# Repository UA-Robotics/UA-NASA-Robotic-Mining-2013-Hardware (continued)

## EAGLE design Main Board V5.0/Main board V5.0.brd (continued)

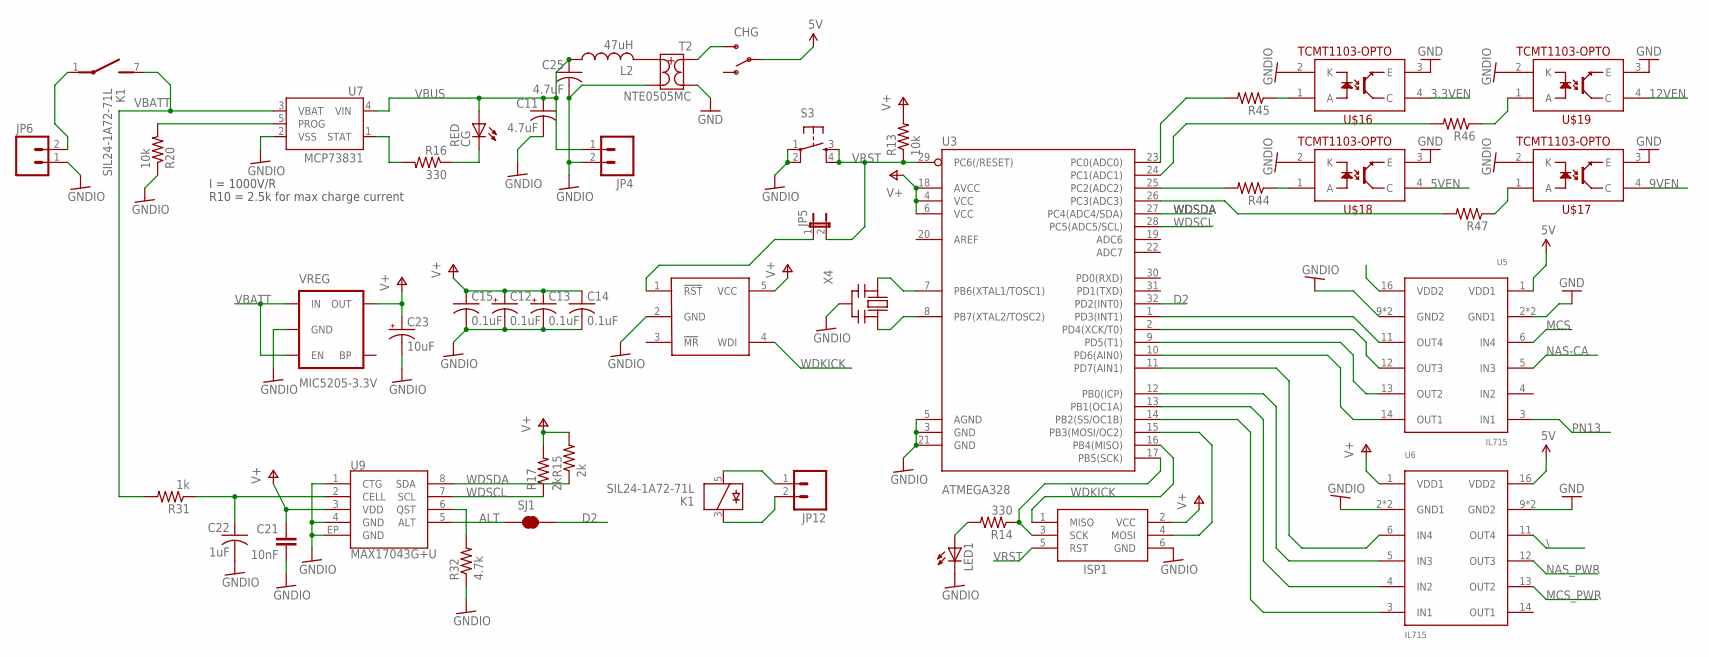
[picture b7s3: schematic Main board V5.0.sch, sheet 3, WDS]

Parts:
C11, C25: 4.7uF; C0603
C12, C13: 0.1uF; CT3528
C14, C15: 0.1uF; C0805
C21: 10nF; 0603-CAP
C22: 1uF; C0603
C23: 10uF; CT3528
CG: RED; SML0805
CHG: SWITCH-SPSTPTH; SWITCH-SPDT
ISP1: AVRISP-6; AVRISP
JP4: M021X02_NO_SILK; 1X02_NO_SILK
JP5: JUMPER-2PTH_LOCK; 1X02_LOCK
JP6: M02-JST-2MM-SMT; JST-2-SMD
JP12: M02POLAR_LOCK; MOLEX-1X2_LOCK
K1: SIL24-1A72-71L; REED
L2: 47uH; L2012C
LED1: LEDCHIPLED_0805; CHIPLED_0805
R13, R20: 10k; R0805
R14, R16: 330; R0805
R15, R17: 2k; R0805
R31: 1k; R0805
R32: 4.7k; R0805
R44, R45, R46, R47: R-US_R0805; R0805
S3: TAC_SWITCHPTH; TACTILE-PTH
SJ1: SOLDERJUMPERTRACE; SJ_2S-TRACE
T2: NTE0505MC; SO-8FT
U3: ATMEGA328; TQFP32-08
U5, U6: IL715; S016
U7: MCP73831; SOT23-5
U9: MAX17043G+U; TDFN-8
U20: MAX823; SOT23-5L
U$16, U$17, U$18, U$19: TCMT1103-OPTO; SSOP-4
VREG: MIC5205-3.3V; SOT23-5
X4: CERMOSCILL-AWCSR; AWCSR

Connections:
3.3VEN: U$16.4 (C); also elsewhere on the board
5V: CHG.2, U5.1 (VDD1), U6.16 (VDD2); also elsewhere on the board
5VEN: U$18.4 (C); also elsewhere on the board
9VEN: U$17.4 (C); also elsewhere on the board
12VEN: U$19.4 (C); also elsewhere on the board
ALT: SJ1.1, U9.5 (ALT)
CELL: C22.1, R31.1, U9.2 (CELL)
D2: SJ1.2, U3.32 (PD2(INT0))
GND: T2.1 (2), U5.2 (GND1), U5.8 (GND1), U6.9 (GND2), U6.15 (GND2), U$16.3 (E), U$17.3 (E), U$18.3 (E), U$19.3 (E); also elsewhere on the board
GNDIO: C11.2, C12.-, C13.-, C14.2, C15.2, C21.2, C22.2, C23.-, C25.2, ISP1.6 (GND), JP4.2, JP6.1, LED1.C, R20.1, R32.1, S3.1, S3.2, T2.7 (3), U3.3 (GND), U3.5 (AGND), U3.21 (GND), U5.9 (GND2), U5.15 (GND2), U6.2 (GND1), U6.8 (GND1), U7.2 (VSS), U9.1 (CTG), U9.4 (GND), U9.EP (GND), U20.2 (GND), U$16.2 (K), U$17.2 (K), U$18.2 (K), U$19.2 (K), VREG.2 (GND), X4.2 (GND)
MCS: U5.6 (IN4); also elsewhere on the board
MCS_PWR: U6.13 (OUT2); also elsewhere on the board
unnamed: JP5.1, U20.1 (!RST)
unnamed: ISP1.3 (SCK), R14.1, U3.17 (PB5(SCK))
unnamed: ISP1.4 (MOSI), U3.15 (PB3(MOSI/OC2))
unnamed: R45.2, U3.23 (PC0(ADC0))
unnamed: L2.2, T2.8 (4)
unnamed: LED1.A, R14.2
unnamed: CG.C, R16.1
unnamed: JP12.1, K1.5
unnamed: JP6.2, K1.1
unnamed: U3.7 (PB6(XTAL1/TOSC1)), X4.1 (IN)
unnamed: U3.8 (PB7(XTAL2/TOSC2)), X4.3 (OUT)
unnamed: U3.2 (PD4(XCK/T0)), U5.12 (OUT3)
unnamed: U3.9 (PD5(T1)), U5.13 (OUT2)
unnamed: U3.10 (PD6(AIN0)), U5.14 (OUT1)
unnamed: CHG.3 (S), T2.3 (1)
unnamed: U3.11 (PD7(AIN1)), U6.6 (IN4)
unnamed: U3.1 (PD3(INT1)), U5.11 (OUT4)
unnamed: R45.1, U$16.1 (A)
unnamed: R46.2, U3.24 (PC1(ADC1))
unnamed: U3.12 (PB0(ICP)), U6.5 (IN3)
unnamed: U3.13 (PB1(OC1A)), U6.4 (IN2)
unnamed: U3.14 (PB2(SS/OC1B)), U6.3 (IN1)
unnamed: R46.1, U$19.1 (A)
unnamed: R44.2, U3.25 (PC2(ADC2))
unnamed: R44.1, U$18.1 (A)
unnamed: R47.2, U3.26 (PC3(ADC3))
unnamed: R47.1, U$17.1 (A)
unnamed: JP12.2, K1.3
NAS-CA: U5.5 (IN3); also elsewhere on the board
NAS_PWR: U6.12 (OUT3); also elsewhere on the board
PN13: U5.3 (IN1); also elsewhere on the board
PROG: R20.2, U7.5 (PROG)
QST: R32.2, U9.6 (QST)
STAT: R16.2, U7.1 (STAT)
V+: C12.+, C13.+, C14.1, C15.1, C21.1, C23.+, ISP1.2 (VCC), R13.2, R15.2, R17.2, U3.4 (VCC), U3.6 (VCC), U3.18 (AVCC), U6.1 (VDD1), U9.3 (VDD), U20.5 (VCC), VREG.5 (OUT)
VBATT: K1.7 (S), R31.2, U7.3 (VBAT), VREG.1 (IN), VREG.3 (EN)
VBUS: C11.1, C25.1, CG.A, JP4.1, L2.1, U7.4 (VIN)
VRST: ISP1.5 (RST), JP5.2, R13.1, S3.3, S3.4, U3.29 (PC6(/RESET))
WDKICK: ISP1.1 (MISO), U3.16 (PB4(MISO)), U20.4 (WDI)
WDSCL: R17.1, U3.28 (PC5(ADC5/SCL)), U9.7 (SCL)
WDSDA: R15.1, U3.27 (PC4(ADC4/SDA)), U9.8 (SDA)
\: U6.11 (OUT4); also elsewhere on the board

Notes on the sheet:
I = 1000V/R
R10 = 2.5k for max charge current

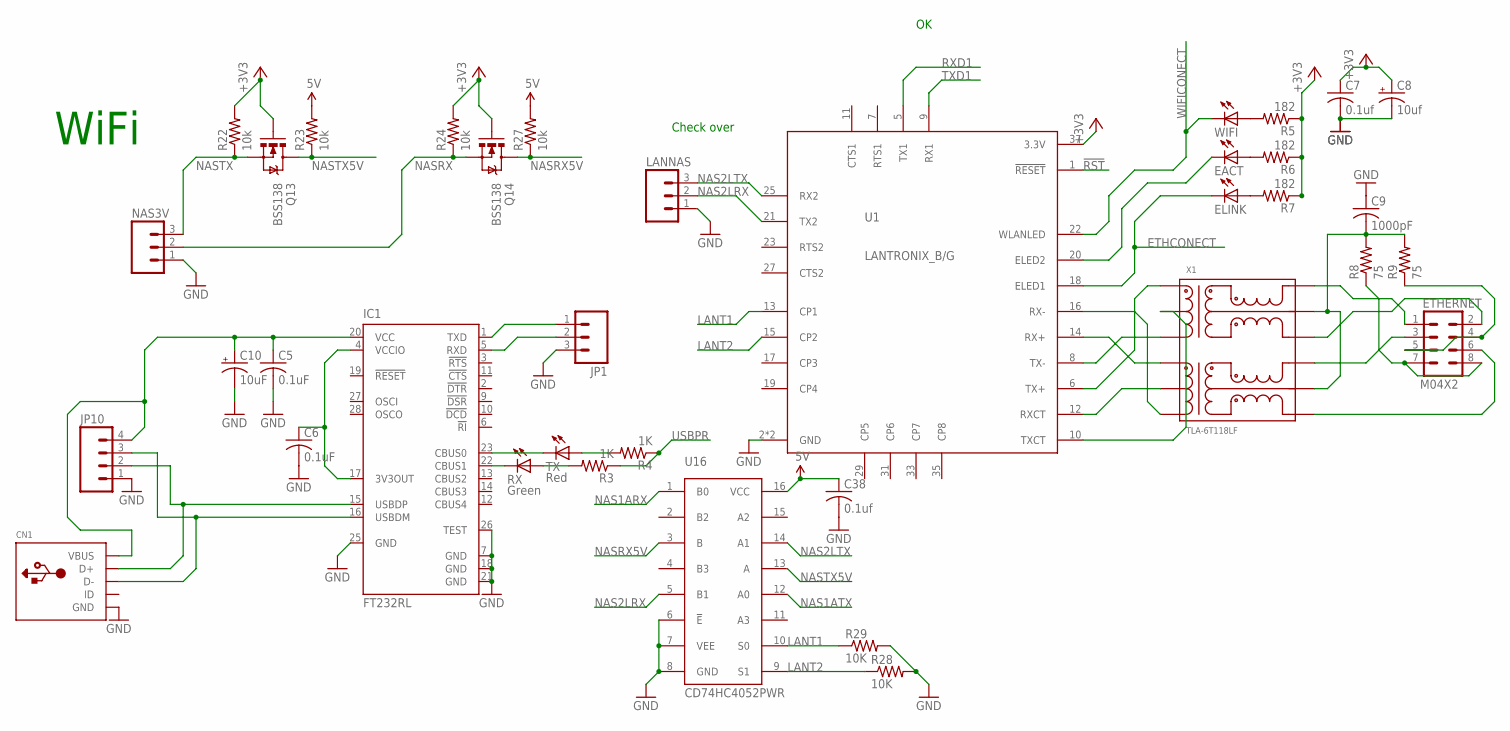
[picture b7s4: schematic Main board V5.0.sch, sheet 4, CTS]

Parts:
C5, C6: 0.1uF; C0805K
C7, C38: 0.1uf; C0805K
C8: 10uf; EIA3528
C9: 1000pF; C1812
C10: 10uF; EIA3528-KIT
CN1: USBMINIB; USB-MINIB
EACT: LEDCHIP-LED0805; CHIP-LED0805
ELINK: LEDCHIP-LED0805; CHIP-LED0805
ETHERNET: M04X2; 2X4
IC1: FT232RL; SSOP28
JP1: M03POLAR; MOLEX-1X3
JP10: M04POLAR; MOLEX-1X4
LANNAS: M03POLAR; MOLEX-1X3
NAS3V: M03LOCK_NO_SILK; 1X03_LOCK_NO_SILK
Q13, Q14: BSS138; SOT23-3
R3, R4: 1K; R0805
R5, R6, R7: 182; R0805
R8, R9: 75; R0805
R22, R23, R24, R27: 10k; R0805
R28, R29: 10K; R0805
RX: Green; CHIP-LED0805
TX: Red; CHIP-LED0805
U1: LANTRONIX_B/G; LANA/BTH
U16: CD74HC4052PWR; TSSOP-16
WIFI: LEDCHIP-LED0805; CHIP-LED0805
X1: TLA-6T118LF; SO-16MOD

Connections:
5V: C38.1, R23.2, R27.2, U16.16 (VCC); also elsewhere on the board
!RST: U1.1 (!RESET)
+3V3: C7.1, C8.A (+), Q13.1 (G), Q14.1 (G), R5.1, R6.1, R7.1, R22.2, R24.2, U1.37 (3.3V); also elsewhere on the board
ETHCONECT: ELINK.C, U1.18 (ELED1)
GND: C5.2, C6.2, C7.2, C8.C (-), C9.1, C10.C (-), C38.2, CN1.GND, IC1.7 (GND), IC1.18 (GND), IC1.21 (GND), IC1.25 (GND), IC1.26 (TEST), JP1.3, JP10.1, LANNAS.1, NAS3V.1, R28.2, R29.2, U1.2 (GND), U1.39 (GND), U16.6 (!E), U16.7 (VEE), U16.8 (GND); also elsewhere on the board
LANT1: R29.1, U1.13 (CP1), U16.10 (S0)
LANT2: R28.1, U1.15 (CP2), U16.9 (S1)
unnamed: IC1.23 (CBUS0), TX.C
unnamed: IC1.22 (CBUS1), RX.C
unnamed: R3.2, RX.A
unnamed: CN1.D+, IC1.15 (USBDP), JP10.2
unnamed: CN1.D-, IC1.16 (USBDM), JP10.3
unnamed: R4.2, TX.A
unnamed: IC1.1 (TXD), JP1.1
unnamed: C6.1, IC1.4 (VCCIO), IC1.17 (3V3OUT)
unnamed: U1.8 (TX-), X1.3
unnamed: U1.6 (TX+), X1.1
unnamed: U1.14 (RX+), X1.6
unnamed: U1.16 (RX-), X1.8
unnamed: U1.12 (RXCT), X1.7
unnamed: U1.10 (TXCT), X1.2
unnamed: ETHERNET.4, ETHERNET.5, R9.1
unnamed: ETHERNET.6, X1.9
unnamed: ETHERNET.3, ETHERNET.7, ETHERNET.8, R8.1, X1.11
unnamed: ETHERNET.2, X1.14
unnamed: ETHERNET.1, X1.16
unnamed: C9.2, R8.2, R9.2, X1.10, X1.15
unnamed: ELINK.A, R7.2
unnamed: EACT.A, R6.2
unnamed: R5.2, WIFI.A
unnamed: EACT.C, U1.20 (ELED2)
unnamed: IC1.5 (RXD), JP1.2
NAS1ARX: U16.1 (B0); also elsewhere on the board
NAS1ATX: U16.12 (A0); also elsewhere on the board
NAS2LRX: LANNAS.2, U1.21 (TX2), U16.5 (B1)
NAS2LTX: LANNAS.3, U1.25 (RX2), U16.14 (A1)
NASRX: NAS3V.2, Q14.2 (S), R24.1; also elsewhere on the board
NASRX5V: Q14.3 (D), R27.1, U16.3 (B)
NASTX: NAS3V.3, Q13.2 (S), R22.1; also elsewhere on the board
NASTX5V: Q13.3 (D), R23.1, U16.13 (A)
RXD1: U1.5 (TX1); also elsewhere on the board
TXD1: U1.9 (RX1); also elsewhere on the board
USBPR: C5.1, C10.A (+), CN1.VBUS, IC1.20 (VCC), JP10.4, R3.1, R4.1
WIFICONECT: U1.22 (WLANLED), WIFI.C

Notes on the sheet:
WiFi
Check over

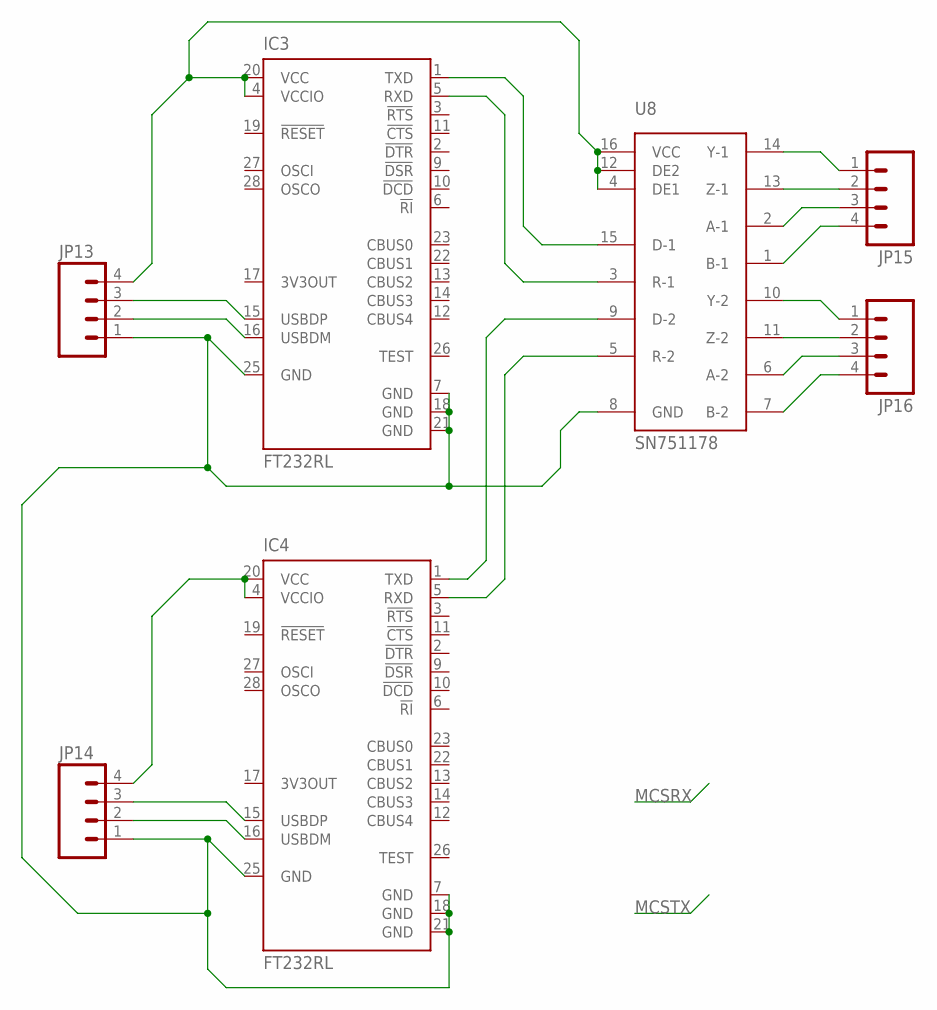
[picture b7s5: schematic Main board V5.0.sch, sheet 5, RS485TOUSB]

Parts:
IC3, IC4: FT232RL; SSOP28
JP13, JP14, JP15, JP16: M04SMD; 1X04-SMD
U8: SN751178; S016

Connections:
unnamed: IC4.1 (TXD), U8.9 (D-2)
unnamed: IC3.15 (USBDP), JP13.3
unnamed: IC3.16 (USBDM), JP13.2
unnamed: IC3.1 (TXD), U8.15 (D-1)
unnamed: IC3.4 (VCCIO), IC3.20 (VCC), JP13.4, U8.4 (DE1), U8.12 (DE2), U8.16 (VCC)
unnamed: IC3.5 (RXD), U8.3 (R-1)
unnamed: IC4.15 (USBDP), JP14.3
unnamed: IC4.16 (USBDM), JP14.2
unnamed: IC4.4 (VCCIO), IC4.20 (VCC), JP14.4
unnamed: IC3.7 (GND), IC3.18 (GND), IC3.21 (GND), IC3.25 (GND), IC4.7 (GND), IC4.18 (GND), IC4.21 (GND), IC4.25 (GND), JP13.1, JP14.1, U8.8 (GND)
unnamed: IC4.5 (RXD), U8.5 (R-2)
unnamed: JP15.1, U8.14 (Y-1)
unnamed: JP15.2, U8.13 (Z-1)
unnamed: JP15.3, U8.2 (A-1)
unnamed: JP15.4, U8.1 (B-1)
unnamed: JP16.1, U8.10 (Y-2)
unnamed: JP16.2, U8.11 (Z-2)
unnamed: JP16.3, U8.6 (A-2)
unnamed: JP16.4, U8.7 (B-2)

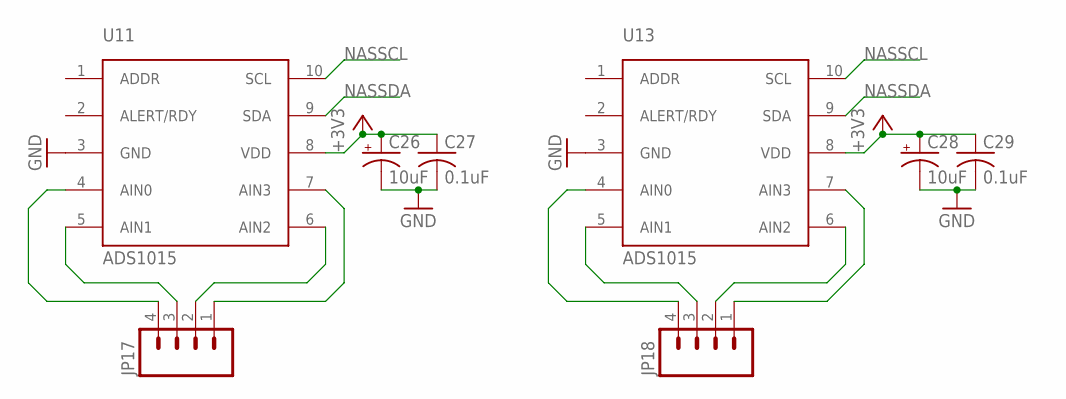
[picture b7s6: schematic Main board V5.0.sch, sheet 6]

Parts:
C26, C28: 10uF; EIA3216-KIT
C27, C29: 0.1uF; C0805
JP17, JP18: M04POLAR; MOLEX-1X4
U11, U13: ADS1015; MSOP-10

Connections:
+3V3: C26.A (+), C27.1, C28.A (+), C29.1, U11.8 (VDD), U13.8 (VDD); also elsewhere on the board
GND: C26.C (-), C27.2, C28.C (-), C29.2, U11.3 (GND), U13.3 (GND); also elsewhere on the board
unnamed: JP17.4, U11.4 (AIN0)
unnamed: JP17.3, U11.5 (AIN1)
unnamed: JP17.2, U11.6 (AIN2)
unnamed: JP17.1, U11.7 (AIN3)
unnamed: JP18.4, U13.4 (AIN0)
unnamed: JP18.3, U13.5 (AIN1)
unnamed: JP18.2, U13.6 (AIN2)
unnamed: JP18.1, U13.7 (AIN3)
NASSCL: U11.10 (SCL), U13.10 (SCL); also elsewhere on the board
NASSDA: U11.9 (SDA), U13.9 (SDA); also elsewhere on the board

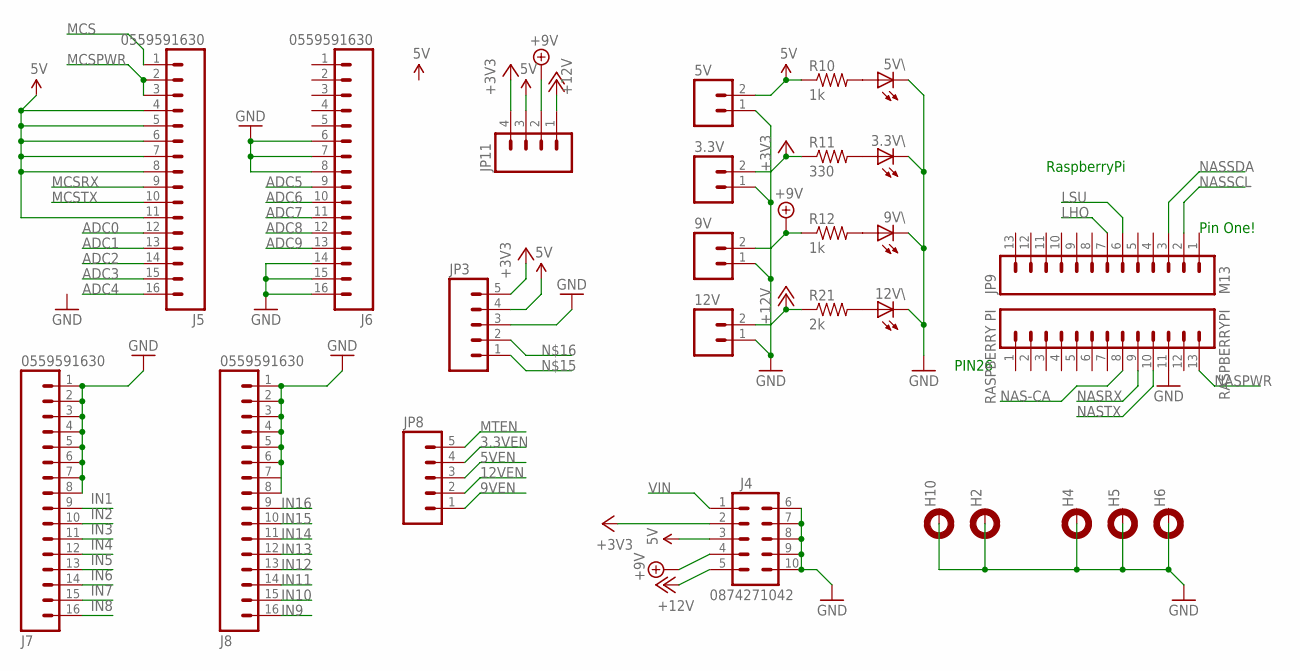
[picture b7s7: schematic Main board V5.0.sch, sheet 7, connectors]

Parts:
3.3V, 5V, 9V, 12V: EUROMAG-290DEG; M2
3.3V\, 5V\, 9V\, 12V\: LED-FKIT-1206; FKIT-LED-1206
H2, H4, H5, H6, H10: MOUNT-PAD-ROUND2.8; 2,8-PAD
J4: 0874271042
J5, J6, J7, J8: 0559591630
JP3, JP8: M05LOCK_LONGPADS; 1X05_LOCK_LONGPADS
JP9: M13; 1X13
JP11: M04POLAR; MOLEX-1X4
R10, R12: 1k; 0805
R11: 330; 0805
R21: 2k; 0805
RASPBERRYPI: RASPBERRY PI; 1X13

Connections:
3.3VEN: JP8.4; also elsewhere on the board
5V: 5V.2, J4.3, J5.4, J5.5, J5.6, J5.7, J5.8, J5.11, JP3.4, JP11.3, R10.1; also elsewhere on the board
5VEN: JP8.3; also elsewhere on the board
9VEN: JP8.1; also elsewhere on the board
12VEN: JP8.2; also elsewhere on the board
+3V3: 3.3V.2, J4.2, JP3.5, JP11.4, R11.1; also elsewhere on the board
+9V: 9V.2, J4.4, JP11.2, R12.1; also elsewhere on the board
+12V: 12V.2, J4.5, JP11.1, R21.1; also elsewhere on the board
ADC0: J5.12; also elsewhere on the board
ADC1: J5.13; also elsewhere on the board
ADC2: J5.14; also elsewhere on the board
ADC3: J5.15; also elsewhere on the board
ADC4: J5.16; also elsewhere on the board
ADC5: J6.9; also elsewhere on the board
ADC6: J6.10; also elsewhere on the board
ADC7: J6.11; also elsewhere on the board
ADC8: J6.12; also elsewhere on the board
ADC9: J6.13; also elsewhere on the board
GND: 3.3V.1, 3.3V\.C, 5V.1, 5V\.C, 9V.1, 9V\.C, 12V.1, 12V\.C, H2.B2,8, H4.B2,8, H5.B2,8, H6.B2,8, H10.B2,8, J4.6, J4.7, J4.8, J4.9, J4.10, J6.6, J6.7, J6.8, J6.14, J6.15, J6.16, J7.1, J7.2, J7.3, J7.4, J7.5, J7.6, J7.7, J7.8, J8.1, J8.2, J8.3, J8.4, J8.5, J8.6, J8.8, JP3.3, RASPBERRYPI.11; also elsewhere on the board
IN1: J7.9; also elsewhere on the board
IN2: J7.10; also elsewhere on the board
IN3: J7.11; also elsewhere on the board
IN4: J7.12; also elsewhere on the board
IN5: J7.13; also elsewhere on the board
IN6: J7.14; also elsewhere on the board
IN7: J7.15; also elsewhere on the board
IN8: J7.16; also elsewhere on the board
IN9: J8.16; also elsewhere on the board
IN10: J8.15; also elsewhere on the board
IN11: J8.14; also elsewhere on the board
IN12: J8.13; also elsewhere on the board
IN13: J8.12; also elsewhere on the board
IN14: J8.11; also elsewhere on the board
IN15: J8.10; also elsewhere on the board
IN16: J8.9; also elsewhere on the board
LHO: JP9.7
LSU: JP9.6
MCS: J5.1; also elsewhere on the board
MCSPWR: J5.2, J5.3; also elsewhere on the board
MCSRX: J5.9; also elsewhere on the board
MCSTX: J5.10; also elsewhere on the board
MTEN: JP8.5
unnamed: 12V\.A, R21.2
unnamed: 9V\.A, R12.2
unnamed: 3.3V\.A, R11.2
unnamed: 5V\.A, R10.2
NAS-CA: RASPBERRYPI.8; also elsewhere on the board
NASPWR: RASPBERRYPI.13; also elsewhere on the board
NASRX: RASPBERRYPI.9; also elsewhere on the board
NASSCL: JP9.2; also elsewhere on the board
NASSDA: JP9.3; also elsewhere on the board
NASTX: RASPBERRYPI.10; also elsewhere on the board
VIN: J4.1

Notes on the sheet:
Pin One!
PIN26
RaspberryPi

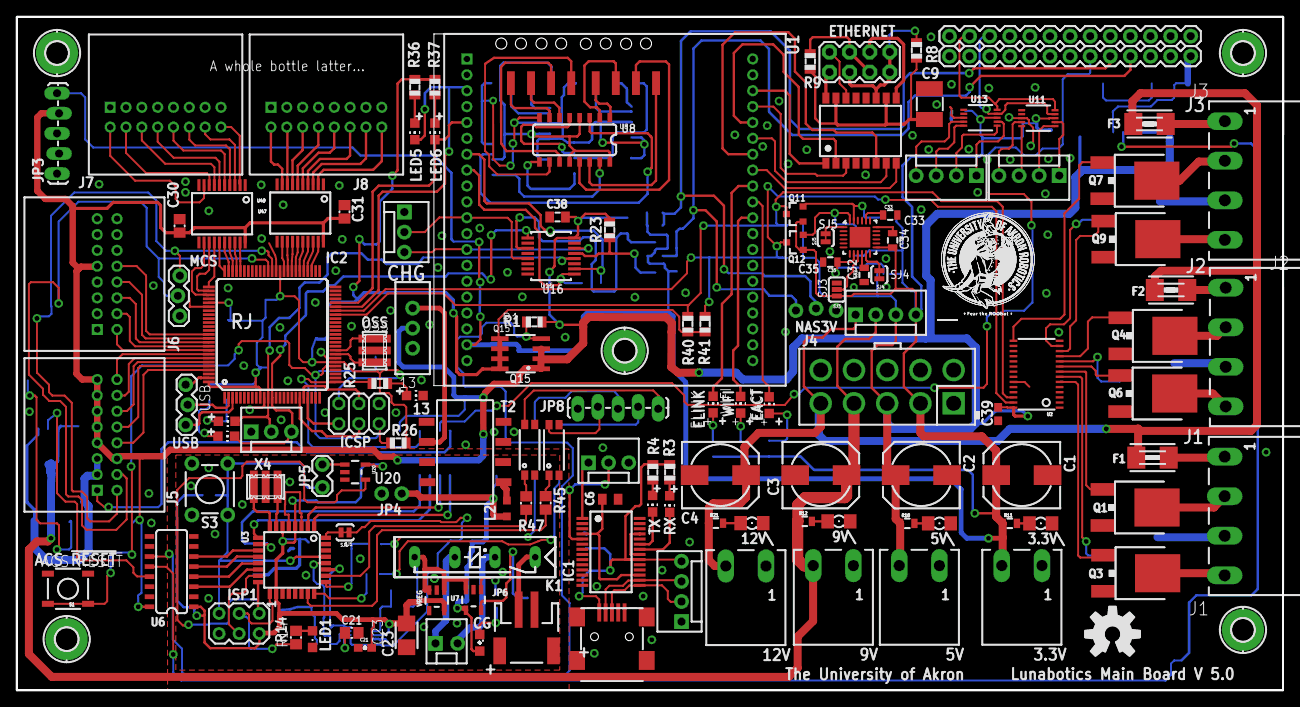
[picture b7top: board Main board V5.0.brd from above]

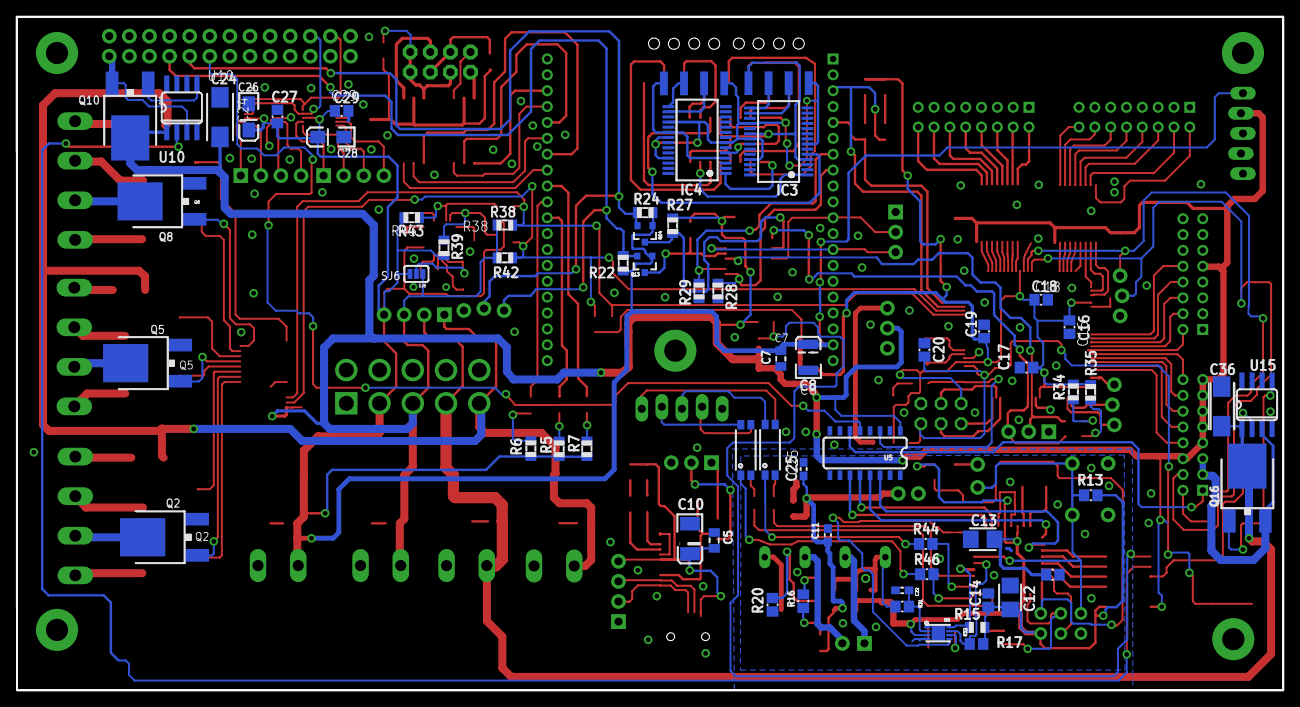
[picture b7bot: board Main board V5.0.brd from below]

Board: 2 copper layers, 160.0 x 85.1 mm, 199 parts (62 on the bottom side), 223 nets.

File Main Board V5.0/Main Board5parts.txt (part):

Partlist

Exported from Main board V5.0.sch at 2/26/2013 11:32:24 PM

EAGLE Version 6.2.0 Copyright (c) 1988-2012 CadSoft

Assembly variant: 

Part        Value                  Device                     Package            Library    Sheet

3.3V                               EUROMAG-290DEG             M2                 NASA_LIB   7
3.3V\                              LED-FKIT-1206              FKIT-LED-1206      SparkFun   7
5V                                 EUROMAG-290DEG             M2                 NASA_LIB   7
5V\                                LED-FKIT-1206              FKIT-LED-1206      SparkFun   7
9V                                 EUROMAG-290DEG             M2                 NASA_LIB   7
9V\                                LED-FKIT-1206              FKIT-LED-1206      SparkFun   7
12V                                EUROMAG-290DEG             M2                 NASA_LIB   7
12V\                               LED-FKIT-1206              FKIT-LED-1206      SparkFun   7
13                                 LEDCHIP-LED0805            CHIP-LED0805       adafruit   1
C1          330uF                  CPOL-US140CLH-0810         140CLH-0810        adafruit   1
C2          330uF                  CPOL-US140CLH-0810         140CLH-0810        adafruit   1
C3          330uf                  CPOL-US140CLH-0810         140CLH-0810        adafruit   1
C4          330uF                  CPOL-US140CLH-0810         140CLH-0810        adafruit   1
C5          0.1uF                  C-USC0805K                 C0805K             adafruit   4
C6          0.1uF                  C-USC0805K                 C0805K             adafruit   4
C7          0.1uf                  C-USC0805K                 C0805K             adafruit   4
C8          10uf                   CAP_POL3528                EIA3528            SparkFun   4
C9          1000pF                 C-USC1812                  C1812              adafruit   4
C10         10uF                   CAP_POL3528-KIT            EIA3528-KIT        SparkFun   4
C11         4.7uF                  C-USC0603                  C0603              resistor   3
C12         0.1uF                  CPOL-USCT3528              CT3528             adafruit   3
C13         0.1uF                  CPOL-USCT3528              CT3528             adafruit   3
C14         0.1uF                  C-USC0805                  C0805              adafruit   3
C15         0.1uF                  C-USC0805                  C0805              adafruit   3
C16         100n                   C-USC0805                  C0805              adafruit   1
C17         100n                   C-USC0805                  C0805              adafruit   1
C18         100n                   C-USC0805                  C0805              adafruit   1
C19         100n                   C-USC0805                  C0805              adafruit   1
C20         22p                    C-USC0805                  C0805              adafruit   1
C21         10nF                   CAP0603-CAP                0603-CAP           SparkFun   3
C22         1uF                    C-USC0603                  C0603              resistor   3
C23         10uF                   CPOL-USCT3528              CT3528             adafruit   3
C24         10uF                   CPOL-USCT6032              CT6032             adafruit   1
C25         4.7uF                  C-USC0603                  C0603              resistor   3
C26         10uF                   CAP_POL1206-KIT            EIA3216-KIT        SparkFun   6
C27         0.1uF                  C-USC0805                  C0805              adafruit   6
C28         10uF                   CAP_POL1206-KIT            EIA3216-KIT        SparkFun   6
C29         0.1uF                  C-USC0805                  C0805              adafruit   6
C30         0.1uF                  C-USC0805                  C0805              adafruit   1
C31         0.1uF                  C-USC0805                  C0805              adafruit   1
C32         0.1uF                  CAP0805                    0805               SparkFun   1
C33         2.2nF                  CAP0805                    0805               SparkFun   1
C34         0.1uF                  CAP0805                    0805               SparkFun   1
C35         10nF                   CAP0805                    0805               SparkFun   1
C36         10uF                   CPOL-USCT6032              CT6032             adafruit   1
C38         0.1uf                  C-USC0805K                 C0805K             adafruit   4
C39         0.1uF                  C-USC0603                  C0603              minimidi   2
CG          RED                    LEDSML0805                 SML0805            led        3
CHG                                SWITCH-SPSTPTH             SWITCH-SPDT        SparkFun   3
CN1                                USBMINIB                   USB-MINIB          adafruit   4
EACT                               LEDCHIP-LED0805            CHIP-LED0805       adafruit   4
ELINK                              LEDCHIP-LED0805            CHIP-LED0805       adafruit   4
ETHERNET    M04X2                  M04X2                      2X4                SparkFun   4
F1          1A                     PTCFUSE-1812               1812               adafruit   2
F2          1A                     PTCFUSE-1812               1812               adafruit   2
F3          1A                     PTCFUSE-1812               1812               adafruit   2
IC1         FT232RL                FT232RL                    SSOP28             ftdichip   4
IC2         ATMEGA1280-16AU        ATMEGA1280-16AU            TQFP100            atmel-2005 1
IC3         FT232RL                FT232RL                    SSOP28             ftdichip   5
IC4         FT232RL                FT232RL                    SSOP28             ftdichip   5
ICSP        ICSP                   PINHD-2X3                  2X03               pinhead    1
ISP1        AVRISP-6               AVRISP-6                   AVRISP             adafruit   3
J1          EUROMAG-4              EUROMAG-4                  M4                 NASA_LIB   2
J2          EUROMAG-4              EUROMAG-4                  M4                 NASA_LIB   2
J3          EUROMAG-4              EUROMAG-4                  M4                 NASA_LIB   2
J4          0874271042             0874271042                 0874271042         NASA_LIB   7
J5          0559591630             0559591630                 0559591630         NASA_LIB   7
J6          0559591630             0559591630                 0559591630         NASA_LIB   7
J7          0559591630             0559591630                 0559591630         NASA_LIB   7
J8          0559591630             0559591630                 0559591630         NASA_LIB   7
JP1                                M03POLAR                   MOLEX-1X3          SparkFun   4
JP3                                M05LOCK_LONGPADS           1X05_LOCK_LONGPADS SparkFun   7
JP4                                M021X02_NO_SILK            1X02_NO_SILK       SparkFun   3
JP5                                JUMPER-2PTH_LOCK           1X02_LOCK          SparkFun   3
JP6                                M02-JST-2MM-SMT            JST-2-SMD          SparkFun   3
JP8                                M05LOCK_LONGPADS           1X05_LOCK_LONGPADS SparkFun   7
JP9         M13                    M13                        1X13               SparkFun   7
JP10                               M04POLAR                   MOLEX-1X4          SparkFun   4
JP11                               M04POLAR                   MOLEX-1X4          SparkFun   7
JP12                               M02POLAR_LOCK              MOLEX-1X2_LOCK     SparkFun   3
JP13                               M04SMD                     1X04-SMD           SparkFun   5
JP14                               M04SMD                     1X04-SMD           SparkFun   5
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
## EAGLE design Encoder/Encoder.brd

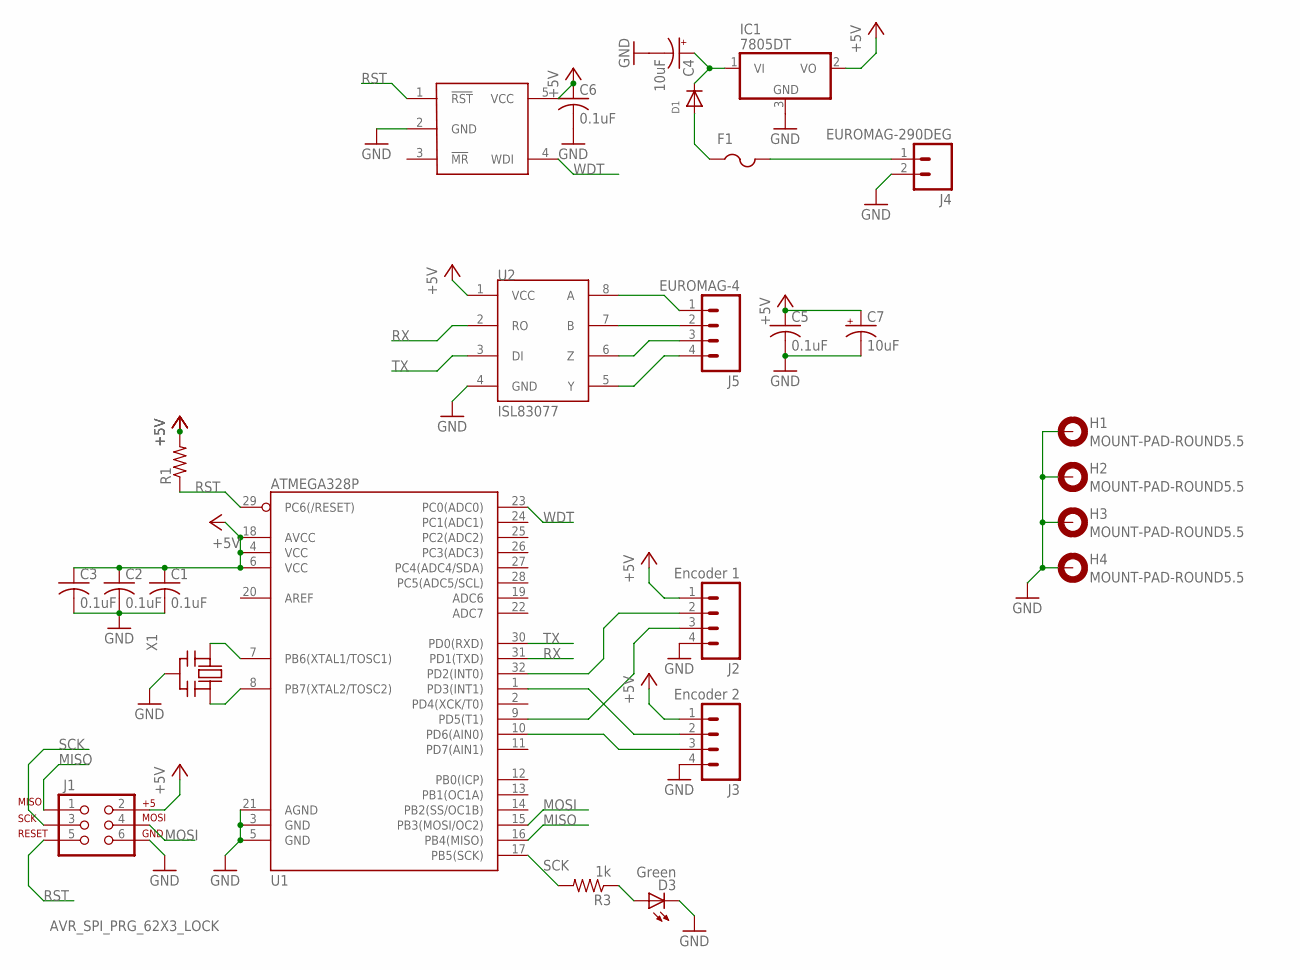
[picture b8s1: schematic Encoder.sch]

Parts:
C1, C2, C3, C5, C6: 0.1uF; C0805
C4, C7: 10uF; CT6032
D1: DIODESMA; SMADIODE
D3: Green; LED-0603
F1: PTCFUSE-1206; R1206
H1, H2, H3, H4: MOUNT-PAD-ROUND5.5; 5,5-PAD
IC1: 7805DT; TO252
J1: AVR_SPI_PRG_62X3_LOCK; 2X3_LOCK
J2: Encoder 1; M4
J3: Encoder 2; M4
J4: EUROMAG-290DEG; M2
J5: EUROMAG-4; M4
R1: RESISTOR0805-RES; 0805
R3: 1k; 0805
U1: ATMEGA328P; TQFP32-08
U2: ISL83077; SO08
U$18: MAX823; SOT23-5L
X1: CERMOSCILL-AWCSR; AWCSR

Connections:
+5V: C1.1, C2.1, C3.1, C5.1, C6.1, C7.+, IC1.2 (VO), J1.2, J2.1, J3.1, R1.2, U1.4 (VCC), U1.6 (VCC), U1.18 (AVCC), U2.1 (VCC), U$18.5 (VCC)
GND: C1.2, C2.2, C3.2, C4.-, C5.2, C6.2, C7.-, D3.C, H1.B5,5, H2.B5,5, H3.B5,5, H4.B5,5, IC1.3 (GND), J1.6, J2.4, J3.4, J4.2, U1.3 (GND), U1.5 (GND), U1.21 (AGND), U2.4 (GND), U$18.2 (GND), X1.2 (GND)
MISO: J1.1, U1.16 (PB4(MISO))
MOSI: J1.4, U1.15 (PB3(MOSI/OC2))
unnamed: J2.2, U1.32 (PD2(INT0))
unnamed: J3.2, U1.1 (PD3(INT1))
unnamed: J3.3, U1.10 (PD6(AIN0))
unnamed: J2.3, U1.9 (PD5(T1))
unnamed: J5.1, U2.8 (A)
unnamed: J5.2, U2.7 (B)
unnamed: J5.3, U2.6 (Z)
unnamed: J5.4, U2.5 (Y)
unnamed: F1.2, J4.1
unnamed: U1.7 (PB6(XTAL1/TOSC1)), X1.1 (IN)
unnamed: D1.A, F1.1
unnamed: U1.8 (PB7(XTAL2/TOSC2)), X1.3 (OUT)
unnamed: C4.+, D1.C, IC1.1 (VI)
unnamed: D3.A, R3.1
RST: J1.5, R1.1, U1.29 (PC6(/RESET)), U$18.1 (!RST)
RX: U1.31 (PD1(TXD)), U2.2 (RO)
SCK: J1.3, R3.2, U1.17 (PB5(SCK))
TX: U1.30 (PD0(RXD)), U2.3 (DI)
WDT: U1.23 (PC0(ADC0)), U$18.4 (WDI)

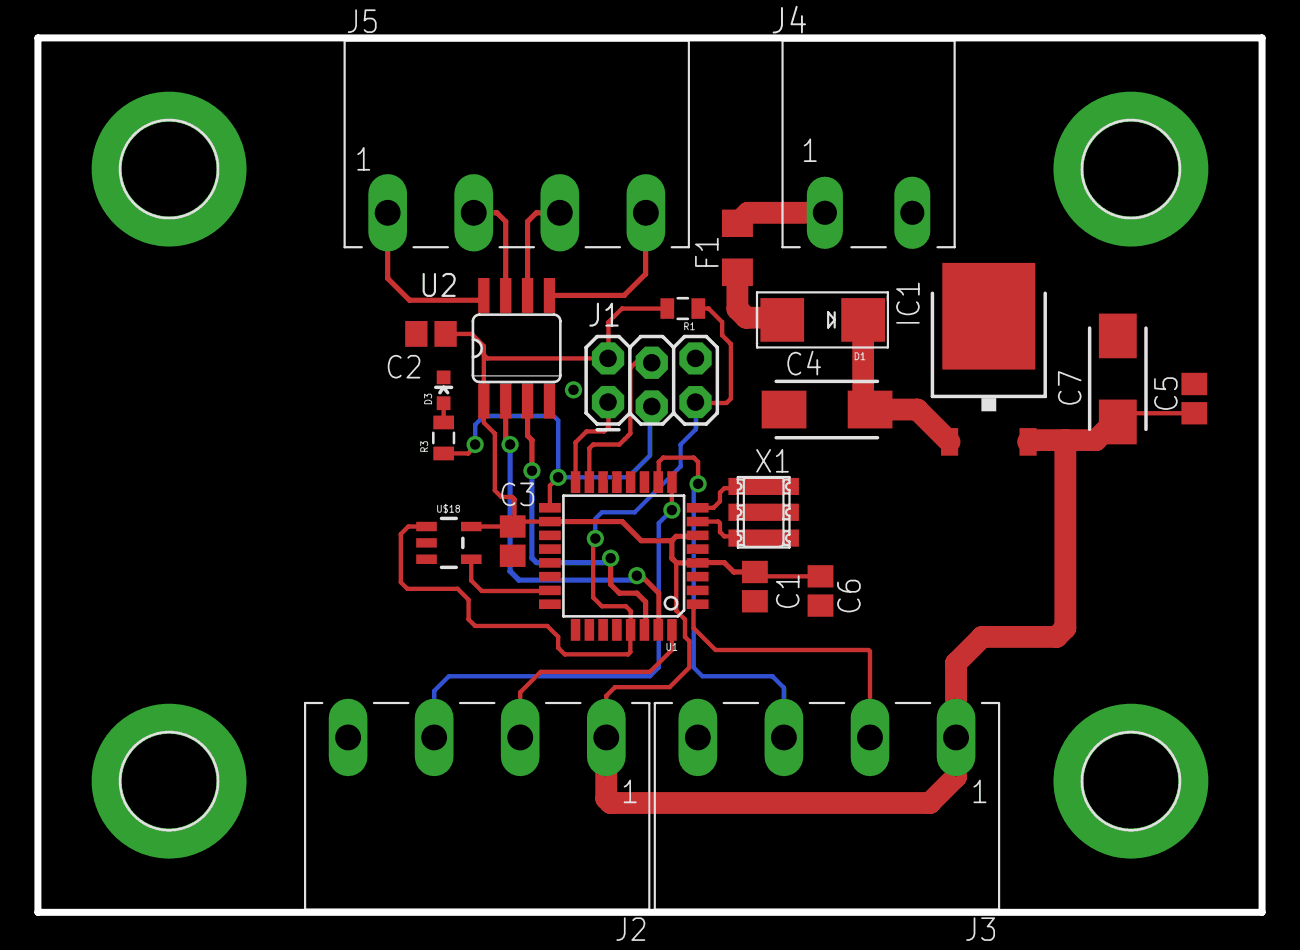
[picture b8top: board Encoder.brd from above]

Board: 2 copper layers, 71.1 x 50.8 mm, 26 parts (0 on the bottom side), 23 nets.

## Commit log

2015-08-14 Initial commit with the hardware schematics from 2013.
